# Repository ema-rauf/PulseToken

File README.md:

# PulseToken

A small, battery-powered hardware 2FA token. It shows one-time login codes on an OLED screen, and only unlocks after your fingerprint is verified.

## Images

<!-- gallery:start -->

<!-- gallery:end -->

## The problem

Phone authenticator apps live on a device that also gets lost, hacked, or runs out of battery. PulseToken keeps your codes on a separate pocket device that nobody else can unlock.

## How it works

1. Press a button to wake PulseToken.
2. Place your finger on the sensor. The fingerprint module checks it on its own, so the fingerprint never leaves the sensor.
3. The real-time clock keeps accurate time, which the time-based codes (TOTP) need.
4. Use the three buttons to pick an account. The 6-digit code appears on the OLED.

## Bill of Materials (BOM)

  | Part | What it's for | Qty | Vendor | Link |
  |---|---|---|---|---|
  | Seeed XIAO ESP32-C3 | Main controller + USB-C LiPo charging | 1 | Seeed Studio | https://www.seeedstudio.com/Seeed-XIAO-ESP32C3-p-5431.html |
  | AS608 optical fingerprint sensor | Unlocks the device | 1 | Colgroad | https://colgroad.com/product/as608-fingerprint-reader-optical-sensor-module/ |
  | 0.96" 128×64 I2C OLED (SSD1306) | Shows the 6-digit codes | 1 | Colgroad | https://colgroad.com/product/0-96-inch-128x64-i2c-oled-display-module/ |
  | DS3231 RTC module | Keeps accurate time for TOTP | 1 | Colgroad | https://colgroad.com/product/ds3231-rtc-real-time-clock-module/ |
  | Tactile push button 6×6×5 mm | Wake and switch accounts | 3 | Colgroad | https://colgroad.com/product/tactile-push-button-switch/ |
  | JST-PH 2.0 mm 2-pin male header | Battery connector on the PCB | 1 | Colgroad | https://colgroad.com/product/jst-male-connector-2-0mm-2-pin-straight/ |
  | 3.7 V 800 mAh LiPo (803035) | Power | 1 | Colgroad | https://colgroad.com/product/3-7v-800mah-803035-2-96wh-lipo-rechargeable-battery/ |
  | 10 kΩ resistor, 1/4 W | Pull-up on the sensor wake line | 1 | Colgroad | https://colgroad.com/product/metal-film-resistors-5-1-4-watt-small-values/ |
  | Jumper wires, 20 cm (pack) | Connect OLED, RTC and sensor to the PCB | 1 | Colgroad | https://colgroad.com/product/20cm-male-to-male-pin-to-pin-jumper-wires-set-20pcs-40pcs/ |
  | Custom PCB, 2-layer, 52.4 × 37.4 mm | Main board | 1 | – | – |

### Printed parts

| # | Qty | Part | File |
|---|---|---|---|
| 1 | 1 | Bottom shell | `cad/pulsetoken_bottom.stl` |
| 2 | 1 | Lid | `cad/pulsetoken_lid.stl` |
| 3 | 3 | Button cap | `cad/pulsetoken_button_cap.stl` |

### Other

| # | Qty | Item | Purpose |
|---|---|---|---|
| 1 | – | PLA or PETG filament (about 40 g) | Case |
| 2 | – | Super glue or hot glue | Holds the OLED in its clips (and the R503 if no nut is used) |

## Enclosure

- Three printed parts: bottom shell, lid, and button cap (print 3).
- Outer size: 75.5 × 42.4 × 34.6 mm.
- The PCB sits on 4 corner supports with locating fences; 4 posts under the lid press it down.
- The LiPo sits in a frame on the floor under the board, with a wire slot up to the JST connector.
- The R503 mounts through a 25.4 mm hole in the lid (its 28 mm ring rests on top).
- The OLED sits in a bay on the left, held by 4 corner clips behind a 23 × 12 mm window.
- The lid snaps on with 4 bumps that click into grooves in the walls.
- USB-C cutout lines up with the XIAO port for charging.
- Tolerances: 0.2 mm lid fit and OLED pocket, 0.3 mm around each button cap, 0.2 mm around the sensor thread, 0.5 mm around the PCB and battery.
- Verified with `cad/fit_check.py` against the real KiCad board model: no collisions between any case part, the board, battery, XIAO, fingerprint sensor or OLED, and every cap sits over its button.

## Files

```
cad/         STEP and STL files,
            pulsetoken_assembly.step (everything in place)
pcb/        KiCad schematic and PCB
images/     Screenshots and renders
```

## Printing

- Bottom shell: print as is, no supports.
- Lid: print upside down (flat top on the bed); the posts and clips then point up, no supports needed.
- Button caps: print 3, flange down.
- PLA or PETG, 0.2 mm layers, 20% infill.

## Assembly

1. Put the LiPo in its frame and run the wires up through the slot to J4.
2. Drop the PCB onto the corner supports.
3. Push the OLED into its clips (a dot of glue keeps it in place) and fit the R503 through its hole.
4. Put the button caps into the lid from below.
5. Connect the module cables, then press the lid down until it clicks.

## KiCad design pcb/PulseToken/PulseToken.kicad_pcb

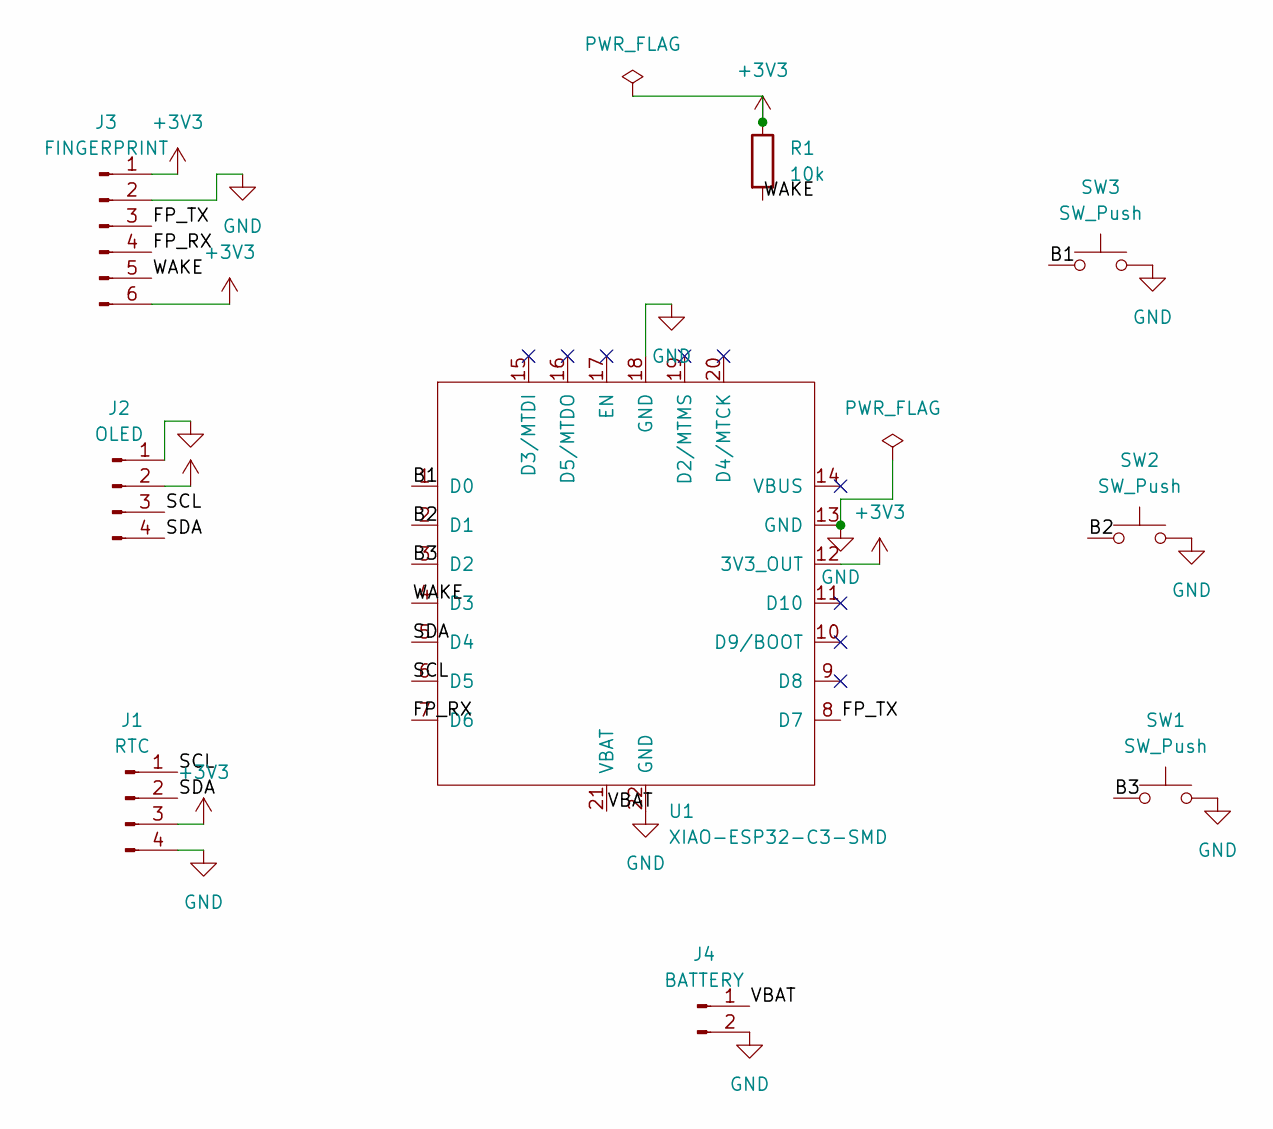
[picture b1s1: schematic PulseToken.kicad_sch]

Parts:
J1: RTC; PinHeader_1x04_P2.54mm_Vertical
J2: OLED; PinHeader_1x04_P2.54mm_Vertical
J3: FINGERPRINT; PinHeader_1x06_P2.54mm_Vertical
J4: BATTERY; JST_PH_B2B-PH-K_1x02_P2.00mm_Vertical
R1: 10k; R_0805_2012Metric_Pad1.20x1.40mm_HandSolder
SW1, SW2, SW3: SW_Push; SW_PUSH_6mm
U1: XIAO-ESP32-C3-SMD

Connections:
+3V3: J1.3, J2.2, J3.1, J3.6, R1.1, U1.12 (3V3_OUT)
/B1: SW3.1, U1.1 (D0)
/B2: SW2.1, U1.2 (D1)
/B3: SW1.1, U1.3 (D2)
/FP_RX: J3.4, U1.7 (D6)
/FP_TX: J3.3, U1.8 (D7)
/SCL: J1.1, J2.3, U1.6 (D5)
/SDA: J1.2, J2.4, U1.5 (D4)
/VBAT: J4.1, U1.21 (VBAT)
/WAKE: J3.5, R1.2, U1.4 (D3)
GND: J1.4, J2.1, J3.2, J4.2, SW1.2, SW2.2, SW3.2, U1.13 (GND), U1.18 (GND), U1.22 (GND)

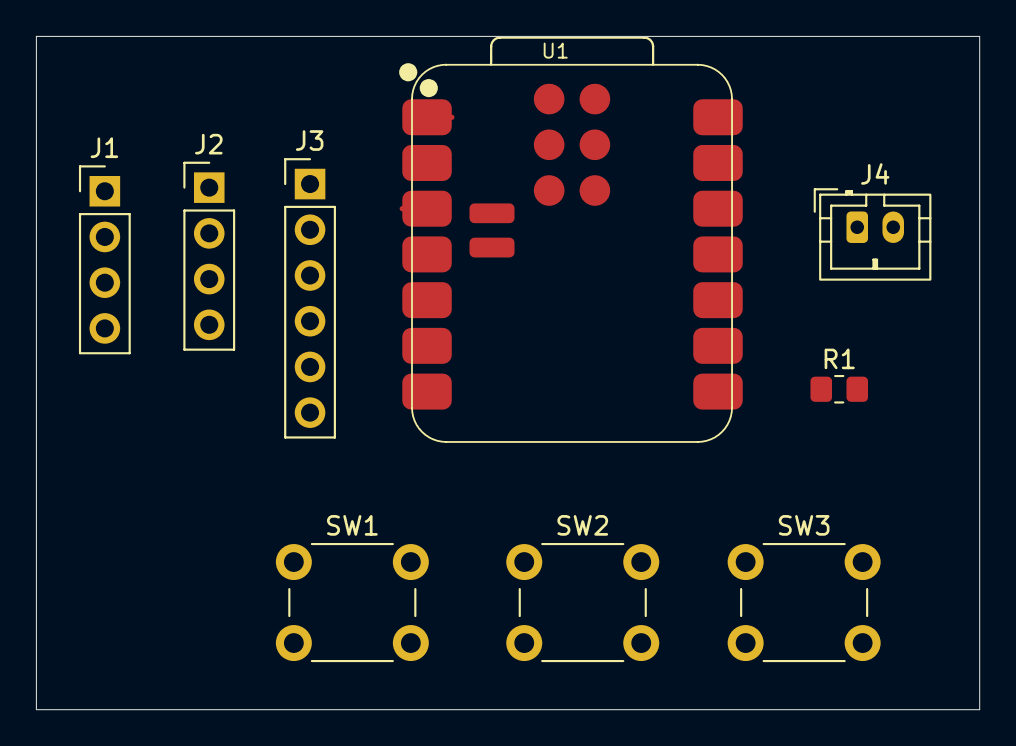
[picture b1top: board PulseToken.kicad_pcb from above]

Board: 2 copper layers, 52.4 x 37.4 mm, 9 parts (0 on the bottom side), 11 nets.
